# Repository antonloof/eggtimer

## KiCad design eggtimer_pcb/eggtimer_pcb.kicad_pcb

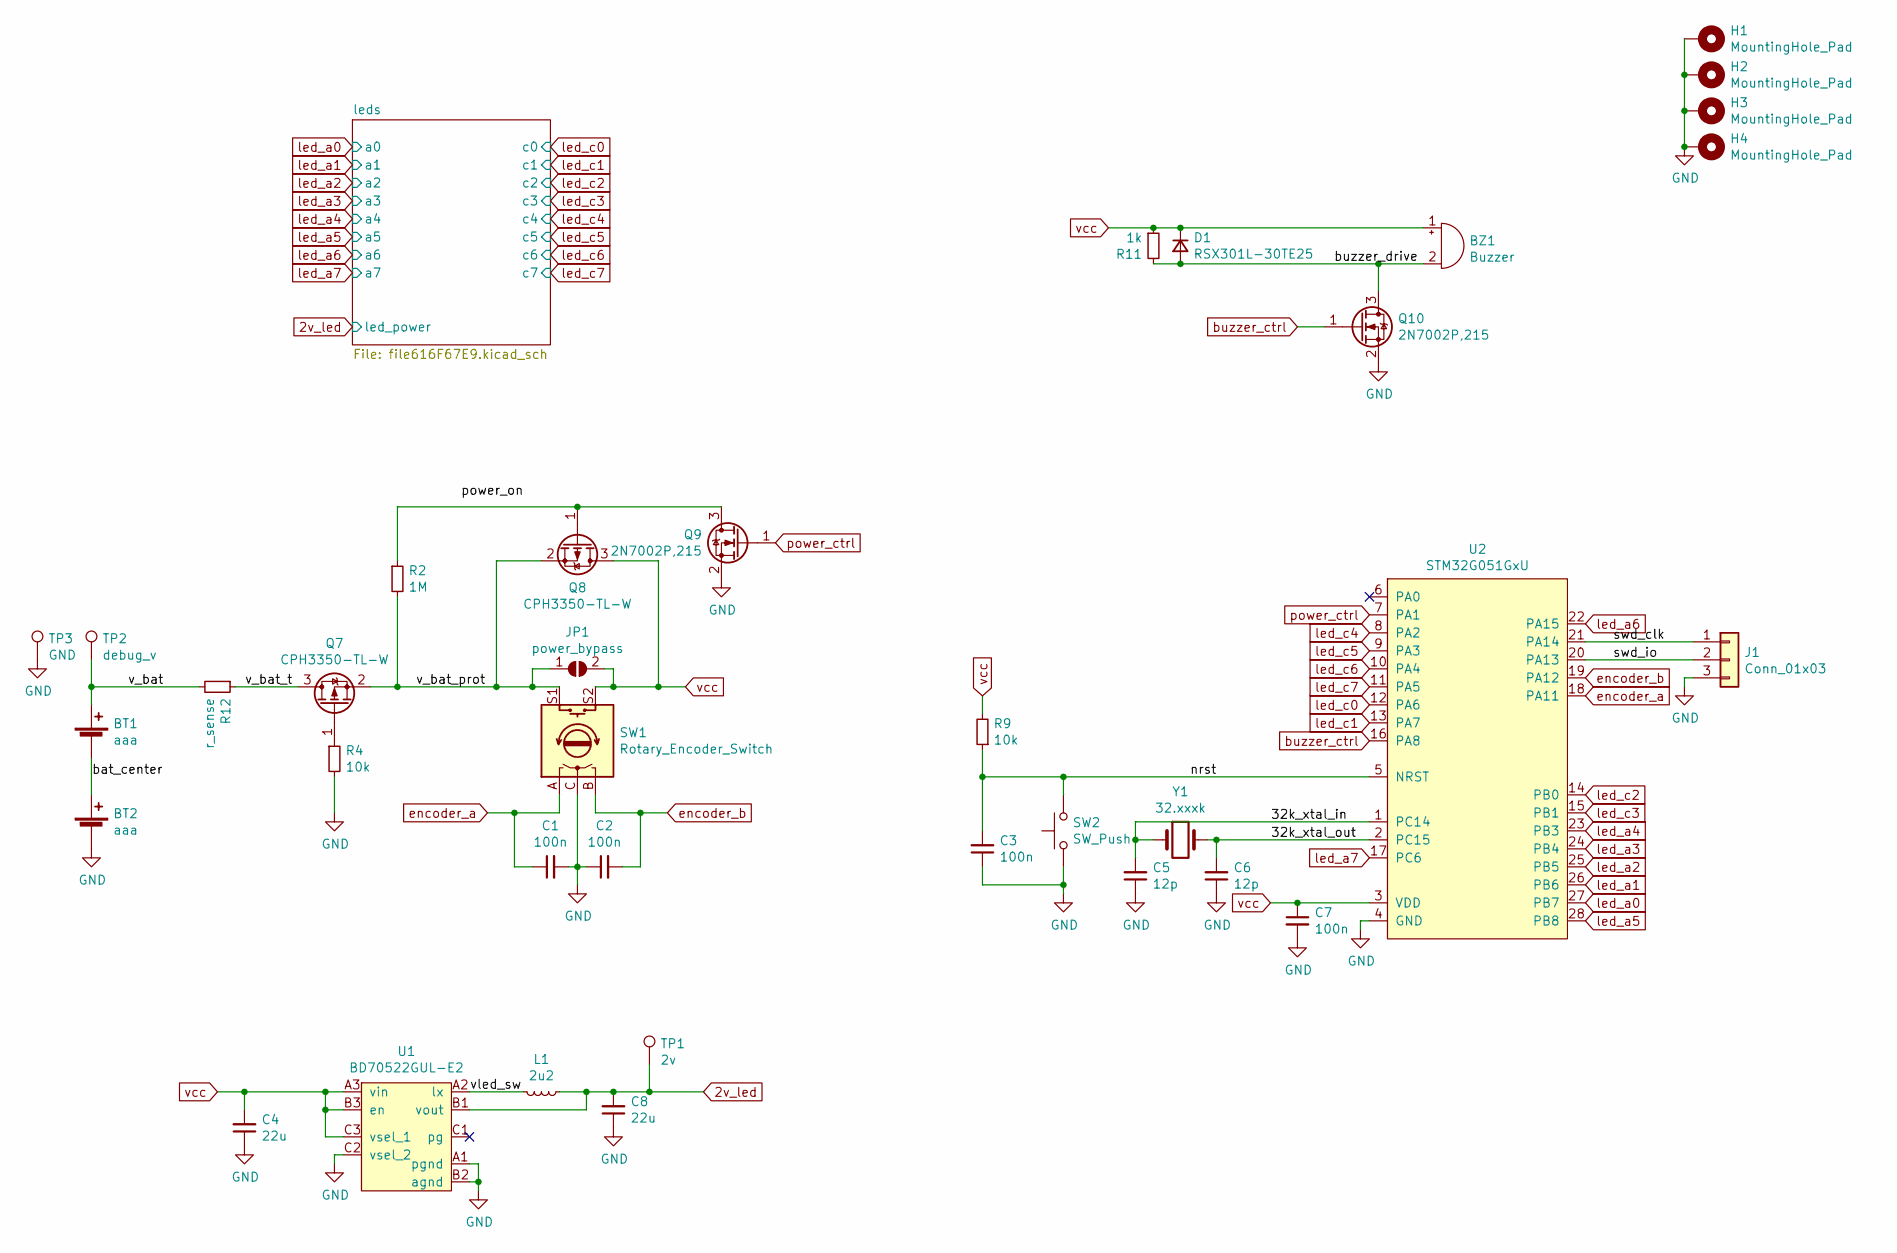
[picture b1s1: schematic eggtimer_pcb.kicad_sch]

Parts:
BT1, BT2: aaa; BatteryHolder_Keystone_2466_1xAAA
BZ1: Buzzer; buzzer_d14_p5
C1, C2, C3, C7: 100n; C_0603_1608Metric
C4, C8: 22u; C_0603_1608Metric
C5, C6: 12p; C_0603_1608Metric
D1: RSX301L-30TE25; smd_diode_sod_106
H1, H2, H3, H4: MountingHole_Pad; MountingHole_2.7mm_M2.5_DIN965_Pad
J1: Conn_01x03; PinHeader_1x03_P2.54mm_Vertical
JP1: power_bypass; SolderJumper-2_P1.3mm_Open_TrianglePad1.0x1.5mm
L1: 2u2; L_Wuerth_MAPI-2010
Q7, Q8: CPH3350-TL-W; SOT-23_Handsoldering
Q9, Q10: 2N7002P,215; SOT-23_Handsoldering
R2: 1M; R_0603_1608Metric_Pad0.98x0.95mm_HandSolder
R4, R9: 10k; R_0603_1608Metric_Pad0.98x0.95mm_HandSolder
R11: 1k; R_0603_1608Metric_Pad0.98x0.95mm_HandSolder
R12: r_sense; R_0603_1608Metric_Pad0.98x0.95mm_HandSolder
SW1: Rotary_Encoder_Switch; RotaryEncoder_Alps_EC11E-Switch_Vertical_H20mm
SW2: SW_Push; push_sw_purple
TP1: 2v; TestPoint_Pad_D2.0mm
TP2: debug_v; TestPoint_Pad_D1.5mm
TP3: GND; TestPoint_Pad_D1.5mm
U1: BD70522GUL-E2; BGA-9_3x3_1.76x1.56mm
U2: STM32G051GxU; QFN-28_4x4mm_P0.5mm
Y1: 32.xxxk; Crystal_Round_D3.0mm_Vertical

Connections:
2v_led: C8.2, L1.1, TP1.1, U1.B1 (vout); also elsewhere on the board
/32k_xtal_in: C6.2, U2.2 (PC15), Y1.2
/32k_xtal_out: C5.2, U2.1 (PC14), Y1.1
/bat_center: BT1.2 (-), BT2.1 (+)
/buzzer_drive: BZ1.2 (+), D1.2 (A), Q10.3 (D), R11.2
/nrst: C3.2, R9.1, SW2.2, U2.5 (NRST)
/swd_clk: J1.1, U2.21 (PA14)
/swd_io: J1.2, U2.20 (PA13)
/v_bat: BT1.1 (+), R12.2, TP2.1
/v_bat_prot: JP1.1 (A), Q7.2 (S), Q8.2 (S), R2.2, SW1.S1
/v_bat_t: Q7.3 (D), R12.1
/vled_sw: L1.2, U1.A2 (lx)
GND: BT2.2 (-), C1.2, C2.1, C3.1, C4.1, C5.1, C6.1, C7.2, C8.1, H1.1, H2.1, H3.1, H4.1, J1.3, Q9.2 (S), Q10.2 (S), R4.2, SW1.C, SW2.1, TP3.1, U1.A1 (pgnd), U1.B2 (agnd), U1.C2 (vsel_2), U2.4 (GND)
unnamed: Q7.1 (G), R4.1
unnamed: Q8.1 (G), Q9.3 (D), R2.1
buzzer_ctrl: Q10.1 (G), U2.16 (PA8)
encoder_a: C1.1, SW1.A, U2.18 (PA11)
encoder_b: C2.2, SW1.B, U2.19 (PA12)
led_a0: U2.27 (PB7); also elsewhere on the board
led_a1: U2.26 (PB6); also elsewhere on the board
led_a2: U2.25 (PB5); also elsewhere on the board
led_a3: U2.24 (PB4); also elsewhere on the board
led_a4: U2.23 (PB3); also elsewhere on the board
led_a5: U2.28 (PB8); also elsewhere on the board
led_a6: U2.22 (PA15); also elsewhere on the board
led_a7: U2.17 (PC6); also elsewhere on the board
led_c0: U2.12 (PA6); also elsewhere on the board
led_c1: U2.13 (PA7); also elsewhere on the board
led_c2: U2.14 (PB0); also elsewhere on the board
led_c3: U2.15 (PB1); also elsewhere on the board
led_c4: U2.8 (PA2); also elsewhere on the board
led_c5: U2.9 (PA3); also elsewhere on the board
led_c6: U2.10 (PA4); also elsewhere on the board
led_c7: U2.11 (PA5); also elsewhere on the board
power_ctrl: Q9.1 (G), U2.7 (PA1)
vcc: BZ1.1 (-), C4.2, C7.1, D1.1 (K), JP1.2 (B), Q8.3 (D), R9.2, R11.1, SW1.S2, U1.A3 (vin), U1.B3 (en), U1.C3 (vsel_1), U2.3 (VDD)

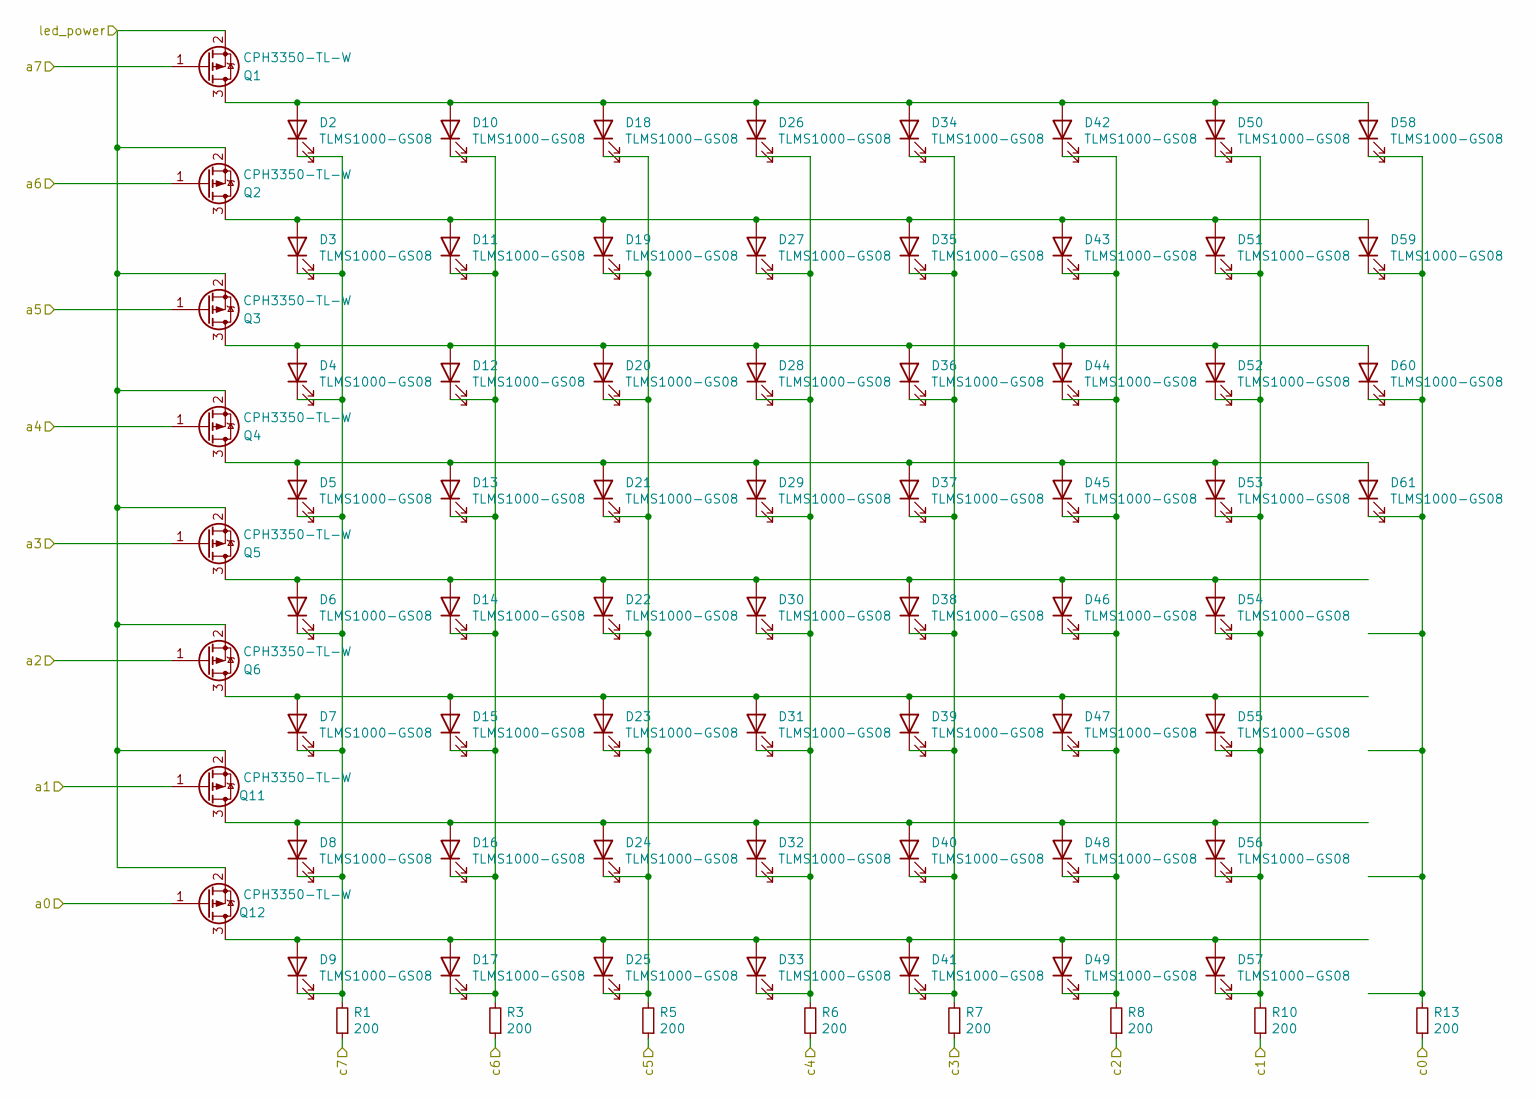
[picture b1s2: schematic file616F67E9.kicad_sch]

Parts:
D2, D3, D4, D5, D6, D7, D8, D9, D10, D11, D12, D13, D14, D15, D16, D17, D18, D19, D20, D21, D22, D23, D24, D25, D26, D27, D28, D29, D30, D31, D32, D33, D34, D35, D36, D37, D38, D39, D40, D41, D42, D43, D44, D45, D46, D47, D48, D49, D50, D51, D52, D53, D54, D55, D56, D57, D58, D59, D60, D61: TLMS1000-GS08; LED_0603_1608Metric_Pad1.05x0.95mm_HandSolder
Q1, Q2, Q3, Q4, Q5, Q6, Q11, Q12: CPH3350-TL-W; SOT-23_Handsoldering
R1, R3, R5, R6, R7, R8, R10, R13: 200; R_0603_1608Metric_Pad0.98x0.95mm_HandSolder

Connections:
2v_led: Q1.2 (S), Q2.2 (S), Q3.2 (S), Q4.2 (S), Q5.2 (S), Q6.2 (S), Q11.2 (S), Q12.2 (S); also elsewhere on the board
unnamed: D2.1 (K), D3.1 (K), D4.1 (K), D5.1 (K), D6.1 (K), D7.1 (K), D8.1 (K), D9.1 (K), R1.2
unnamed: D10.1 (K), D11.1 (K), D12.1 (K), D13.1 (K), D14.1 (K), D15.1 (K), D16.1 (K), D17.1 (K), R3.2
unnamed: D2.2 (A), D10.2 (A), D18.2 (A), D26.2 (A), D34.2 (A), D42.2 (A), D50.2 (A), D58.2 (A), Q1.3 (D)
unnamed: D3.2 (A), D11.2 (A), D19.2 (A), D27.2 (A), D35.2 (A), D43.2 (A), D51.2 (A), D59.2 (A), Q2.3 (D)
unnamed: D4.2 (A), D12.2 (A), D20.2 (A), D28.2 (A), D36.2 (A), D44.2 (A), D52.2 (A), D60.2 (A), Q3.3 (D)
unnamed: D5.2 (A), D13.2 (A), D21.2 (A), D29.2 (A), D37.2 (A), D45.2 (A), D53.2 (A), D61.2 (A), Q4.3 (D)
unnamed: D6.2 (A), D14.2 (A), D22.2 (A), D30.2 (A), D38.2 (A), D46.2 (A), D54.2 (A), Q5.3 (D)
unnamed: D7.2 (A), D15.2 (A), D23.2 (A), D31.2 (A), D39.2 (A), D47.2 (A), D55.2 (A), Q6.3 (D)
unnamed: D8.2 (A), D16.2 (A), D24.2 (A), D32.2 (A), D40.2 (A), D48.2 (A), D56.2 (A), Q11.3 (D)
unnamed: D9.2 (A), D17.2 (A), D25.2 (A), D33.2 (A), D41.2 (A), D49.2 (A), D57.2 (A), Q12.3 (D)
unnamed: D18.1 (K), D19.1 (K), D20.1 (K), D21.1 (K), D22.1 (K), D23.1 (K), D24.1 (K), D25.1 (K), R5.2
unnamed: D26.1 (K), D27.1 (K), D28.1 (K), D29.1 (K), D30.1 (K), D31.1 (K), D32.1 (K), D33.1 (K), R6.2
unnamed: D34.1 (K), D35.1 (K), D36.1 (K), D37.1 (K), D38.1 (K), D39.1 (K), D40.1 (K), D41.1 (K), R7.2
unnamed: D42.1 (K), D43.1 (K), D44.1 (K), D45.1 (K), D46.1 (K), D47.1 (K), D48.1 (K), D49.1 (K), R8.2
unnamed: D50.1 (K), D51.1 (K), D52.1 (K), D53.1 (K), D54.1 (K), D55.1 (K), D56.1 (K), D57.1 (K), R10.2
unnamed: D58.1 (K), D59.1 (K), D60.1 (K), D61.1 (K), R13.2
led_a0: Q12.1 (G); also elsewhere on the board
led_a1: Q11.1 (G); also elsewhere on the board
led_a2: Q6.1 (G); also elsewhere on the board
led_a3: Q5.1 (G); also elsewhere on the board
led_a4: Q4.1 (G); also elsewhere on the board
led_a5: Q3.1 (G); also elsewhere on the board
led_a6: Q2.1 (G); also elsewhere on the board
led_a7: Q1.1 (G); also elsewhere on the board
led_c0: R13.1; also elsewhere on the board
led_c1: R10.1; also elsewhere on the board
led_c2: R8.1; also elsewhere on the board
led_c3: R7.1; also elsewhere on the board
led_c4: R6.1; also elsewhere on the board
led_c5: R5.1; also elsewhere on the board
led_c6: R3.1; also elsewhere on the board
led_c7: R1.1; also elsewhere on the board

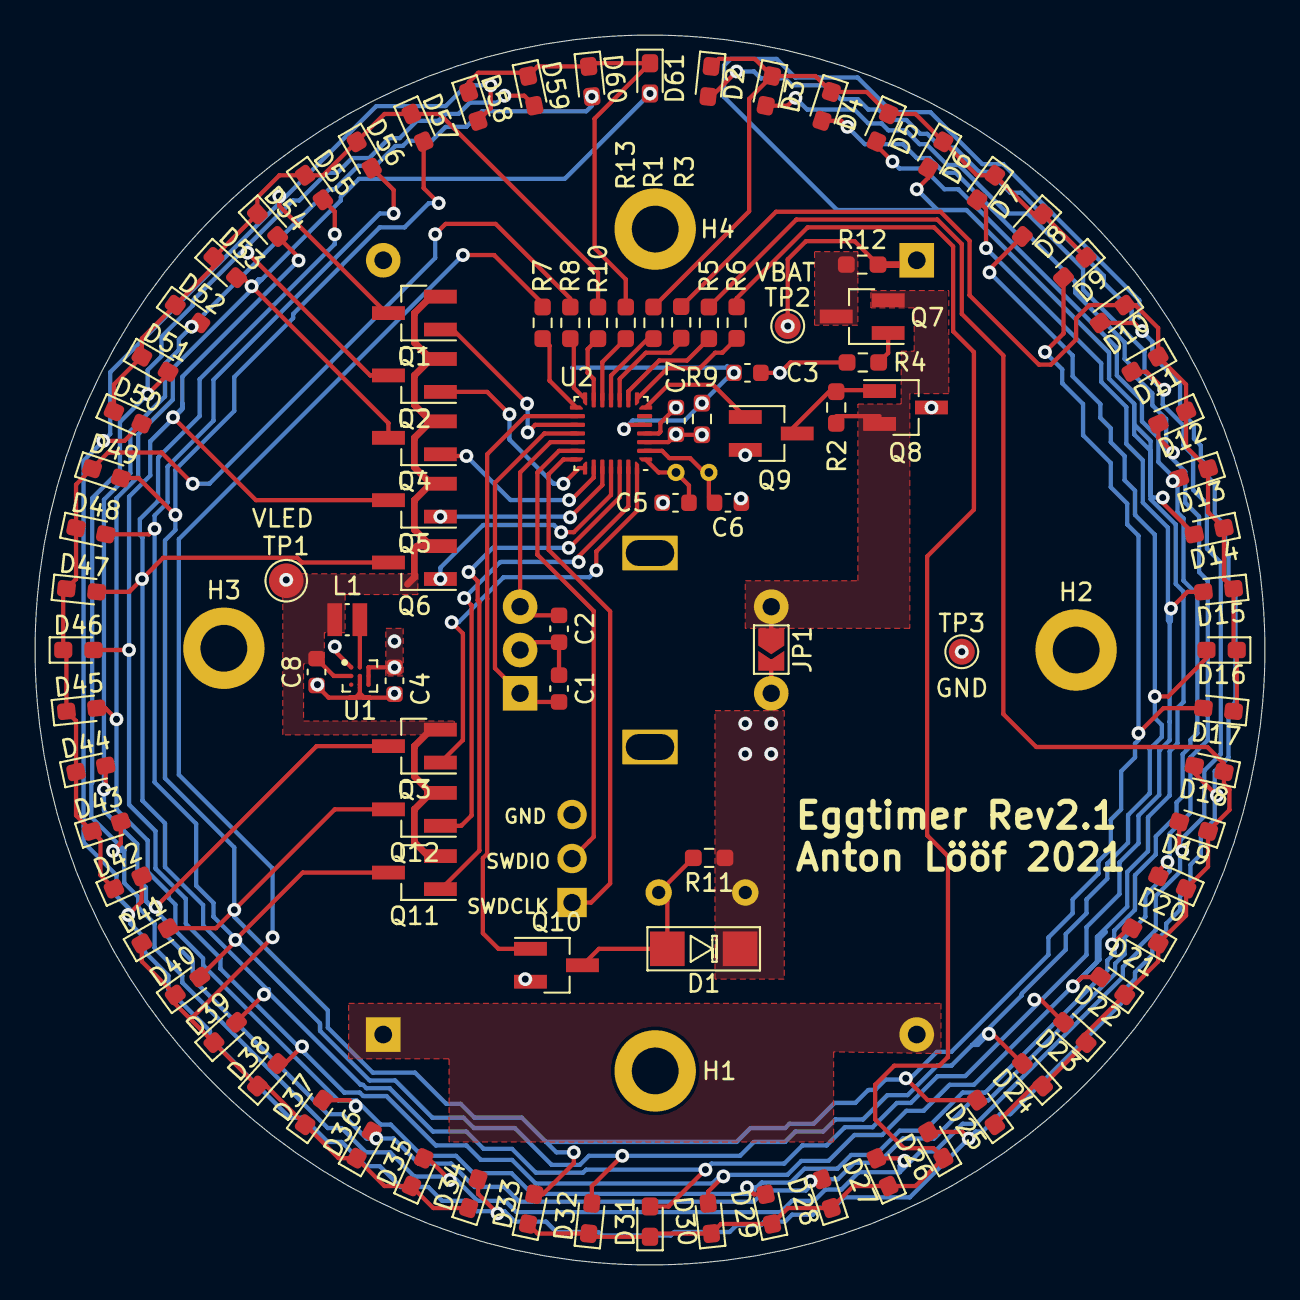
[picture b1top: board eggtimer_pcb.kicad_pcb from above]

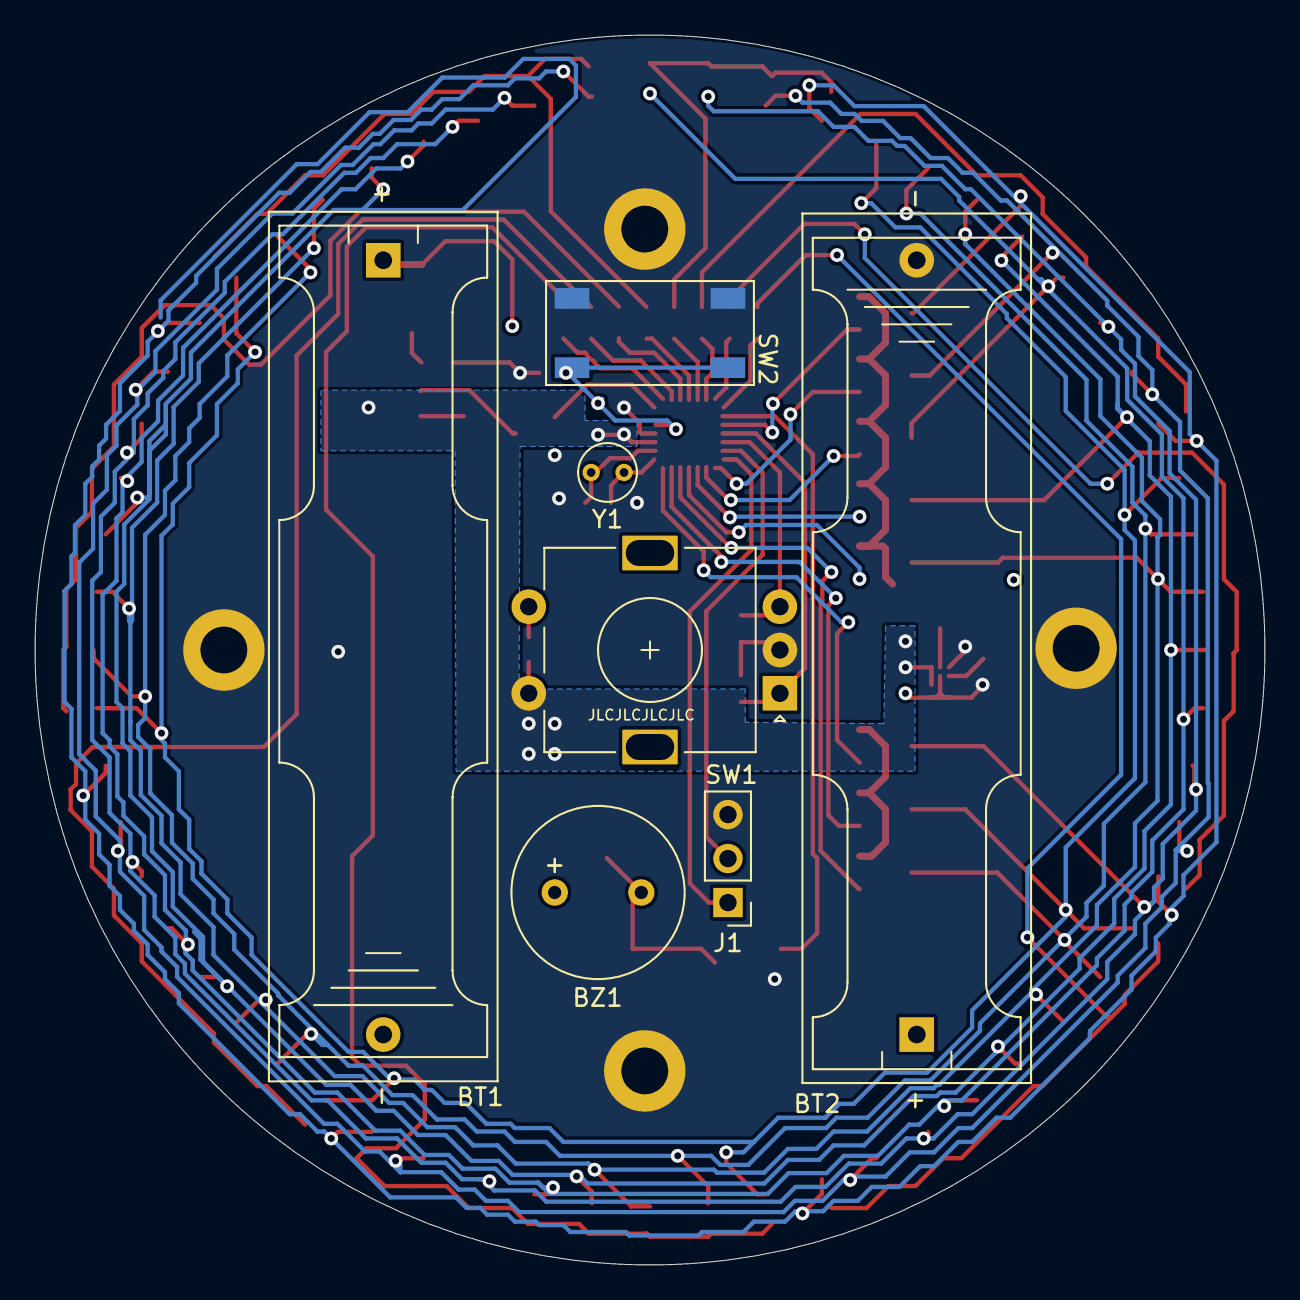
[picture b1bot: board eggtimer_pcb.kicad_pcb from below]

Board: 2 copper layers, 71.0 x 71.0 mm, 112 parts (7 on the bottom side), 52 nets.

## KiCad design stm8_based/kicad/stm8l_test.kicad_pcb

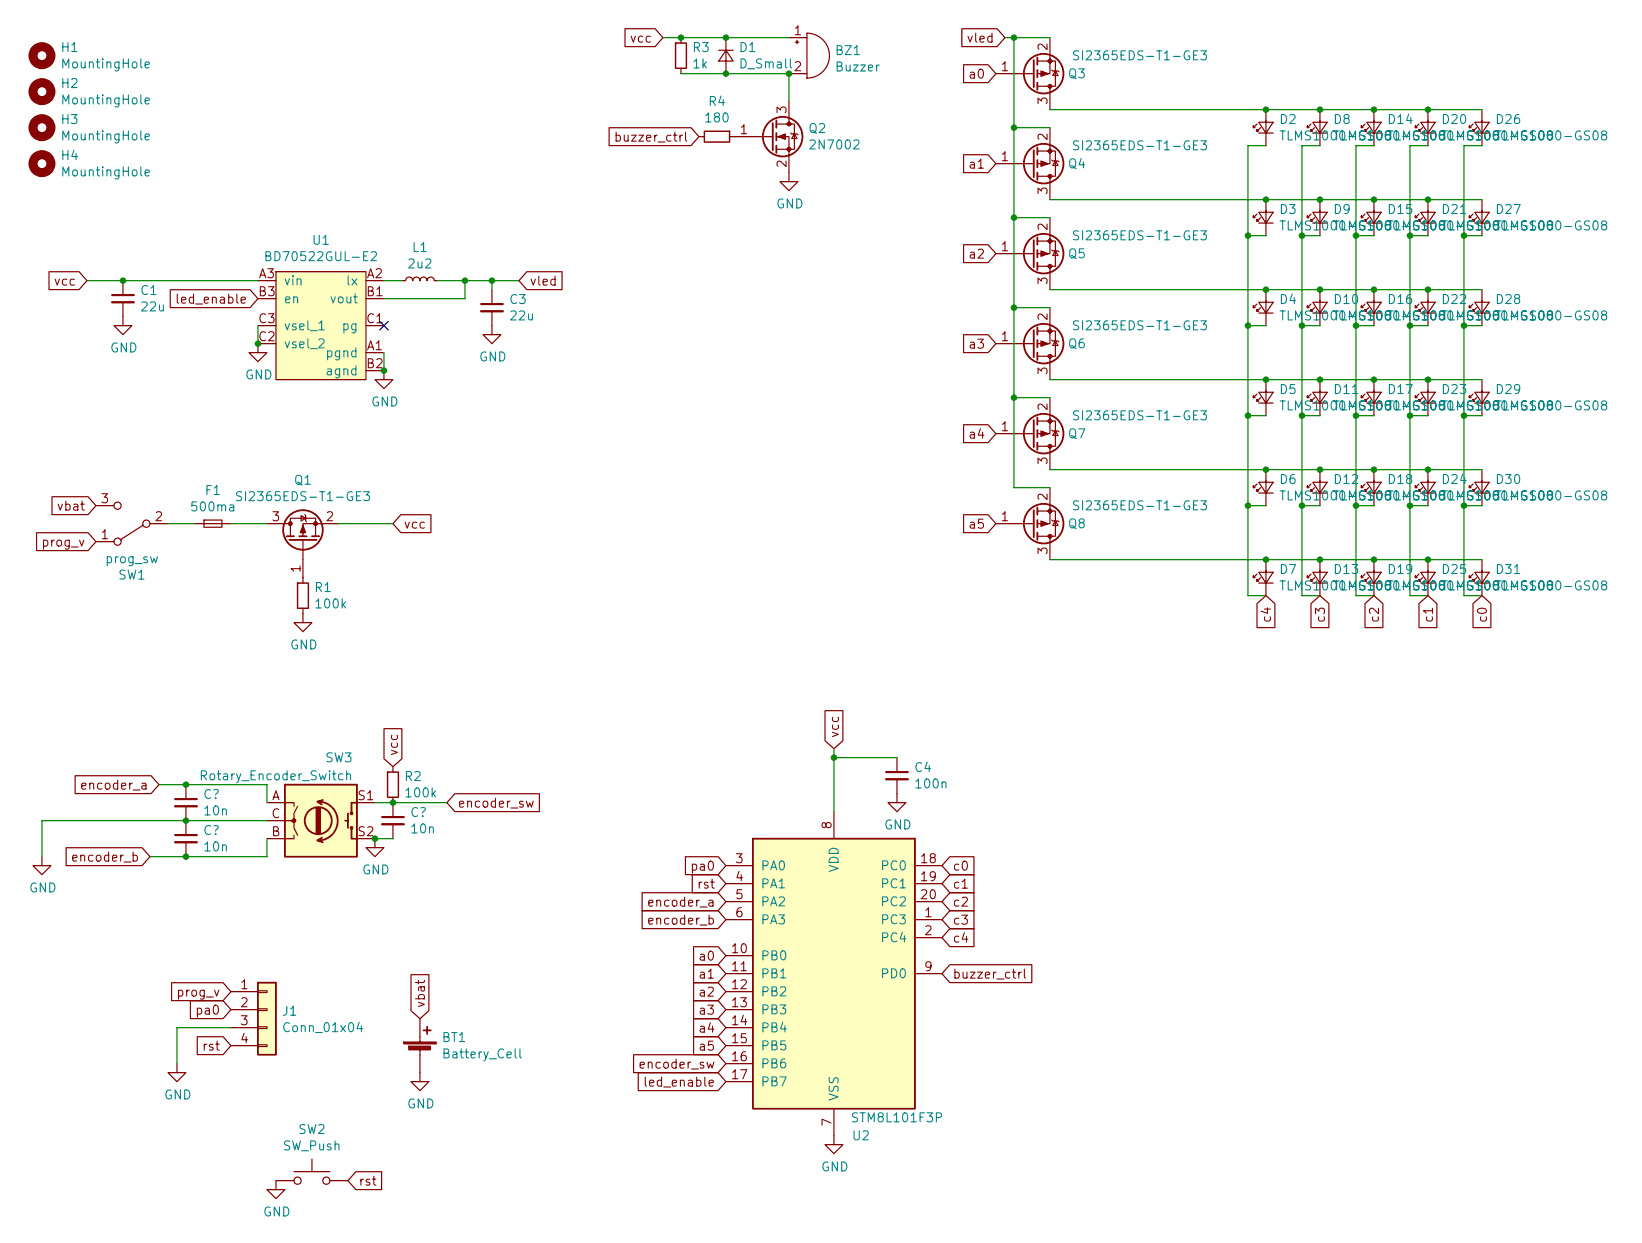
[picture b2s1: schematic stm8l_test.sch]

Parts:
BT1: Battery_Cell; BatteryHolder_Keystone_3002_1x2032
BZ1: Buzzer; buzzer_d14_p5
C1, C3: 22u; C_0603_1608Metric_Pad1.05x0.95mm_HandSolder
C4: 100n; C_0603_1608Metric_Pad1.05x0.95mm_HandSolder
D1: D_Small; D_1210_3225Metric_Pad1.42x2.65mm_HandSolder
D2, D3, D4, D5, D6, D7, D8, D9, D10, D11, D12, D13, D14, D15, D16, D17, D18, D19, D20, D21, D22, D23, D24, D25, D26, D27, D28, D29, D30, D31: TLMS1000-GS08; LED_0603_1608Metric_Pad1.05x0.95mm_HandSolder
F1: 500ma; Fuse_1206_3216Metric_Pad1.42x1.75mm_HandSolder
H1, H2, H3, H4: MountingHole; MountingHole_2.7mm_M2.5
J1: Conn_01x04; TSM-104-01-L-SH
L1: 2u2; L_Wuerth_WE-PD-Typ-7345
Q1, Q3, Q4, Q5, Q6, Q7, Q8: SI2365EDS-T1-GE3; SOT-23_Handsoldering
Q2: 2N7002; SOT-23
R1, R2: 100k; R_0603_1608Metric_Pad1.05x0.95mm_HandSolder
R3: 1k; R_0603_1608Metric_Pad1.05x0.95mm_HandSolder
R4: 180; R_0603_1608Metric_Pad1.05x0.95mm_HandSolder
SW1: prog_sw; TSM-103-01-l_SH
SW2: SW_Push; push_sw_purple
SW3: Rotary_Encoder_Switch; RotaryEncoder_Alps_EC11E-Switch_Vertical_H20mm
U1: BD70522GUL-E2; BGA-9_3x3_1.76x1.56mm
U2: STM8L101F3P; TSSOP-20_4.4x6.5mm_P0.65mm

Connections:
GND: BT1.2 (-), C1.2, C3.2, C4.2, J1.3, Q2.2 (S), R1.2, SW2.1, SW3.C, SW3.S2, U1.A1 (pgnd), U1.B2 (agnd), U1.C2 (vsel_2), U1.C3 (vsel_1), U2.7 (VSS)
unnamed: BZ1.2 (+), D1.2 (A), Q2.3 (D), R3.2
unnamed: D4.2 (A), D10.2 (A), D16.2 (A), D22.2 (A), D28.2 (A), Q5.3 (D)
unnamed: D5.2 (A), D11.2 (A), D17.2 (A), D23.2 (A), D29.2 (A), Q6.3 (D)
unnamed: D6.2 (A), D12.2 (A), D18.2 (A), D24.2 (A), D30.2 (A), Q7.3 (D)
unnamed: D7.2 (A), D13.2 (A), D19.2 (A), D25.2 (A), D31.2 (A), Q8.3 (D)
unnamed: D2.2 (A), D8.2 (A), D14.2 (A), D20.2 (A), D26.2 (A), Q3.3 (D)
unnamed: D3.2 (A), D9.2 (A), D15.2 (A), D21.2 (A), D27.2 (A), Q4.3 (D)
unnamed: F1.1, SW1.2 (B)
unnamed: F1.2, Q1.3 (D)
unnamed: L1.1, U1.A2 (lx)
unnamed: Q1.1 (G), R1.1
unnamed: Q2.1 (G), R4.1
a0: Q3.1 (G), U2.10 (PB0)
a1: Q4.1 (G), U2.11 (PB1)
a2: Q5.1 (G), U2.12 (PB2)
a3: Q6.1 (G), U2.13 (PB3)
a4: Q7.1 (G), U2.14 (PB4)
a5: Q8.1 (G), U2.15 (PB5)
buzzer_ctrl: R4.2, U2.9 (PD0)
c0: D26.1 (K), D27.1 (K), D28.1 (K), D29.1 (K), D30.1 (K), D31.1 (K), U2.18 (PC0)
c1: D20.1 (K), D21.1 (K), D22.1 (K), D23.1 (K), D24.1 (K), D25.1 (K), U2.19 (PC1)
c2: D14.1 (K), D15.1 (K), D16.1 (K), D17.1 (K), D18.1 (K), D19.1 (K), U2.20 (PC2)
c3: D8.1 (K), D9.1 (K), D10.1 (K), D11.1 (K), D12.1 (K), D13.1 (K), U2.1 (PC3)
c4: D2.1 (K), D3.1 (K), D4.1 (K), D5.1 (K), D6.1 (K), D7.1 (K), U2.2 (PC4)
encoder_a: SW3.A, U2.5 (PA2)
encoder_b: SW3.B, U2.6 (PA3)
encoder_sw: R2.2, SW3.S1, U2.16 (PB6)
led_enable: U1.B3 (en), U2.17 (PB7)
pa0: J1.2, U2.3 (PA0)
prog_v: J1.1, SW1.1 (A)
rst: J1.4, SW2.2, U2.4 (PA1)
vled: C3.1, L1.2, Q3.2 (S), Q4.2 (S), Q5.2 (S), Q6.2 (S), Q7.2 (S), Q8.2 (S), U1.B1 (vout)

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
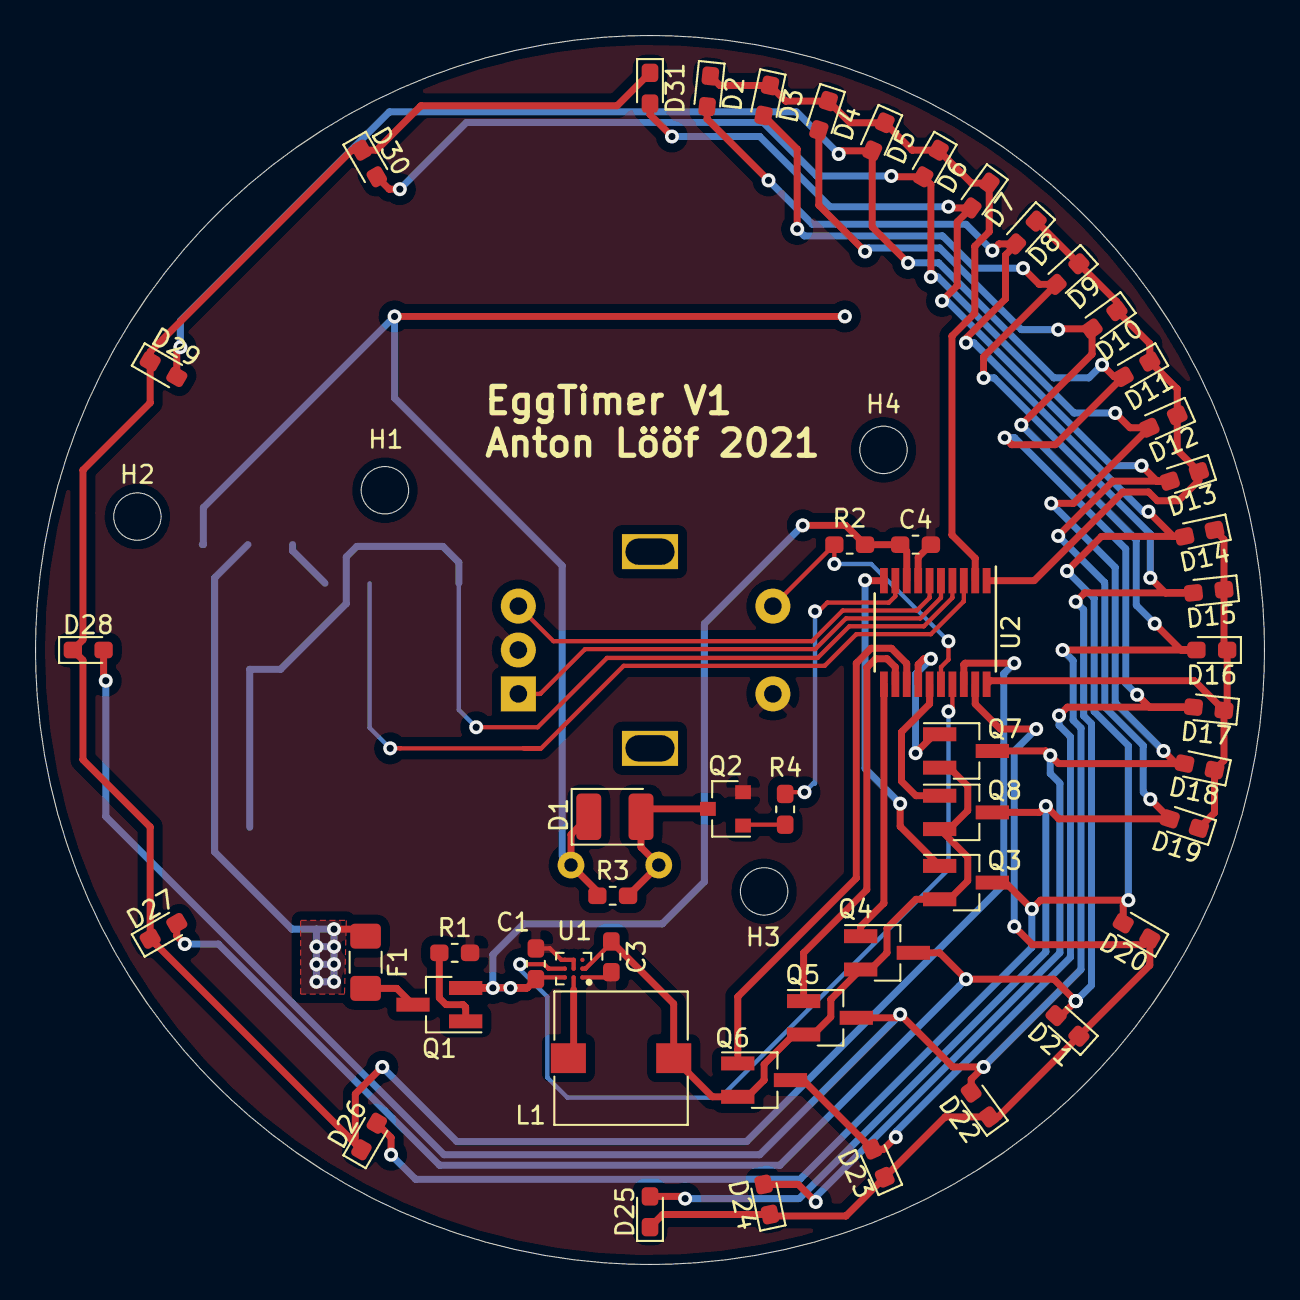
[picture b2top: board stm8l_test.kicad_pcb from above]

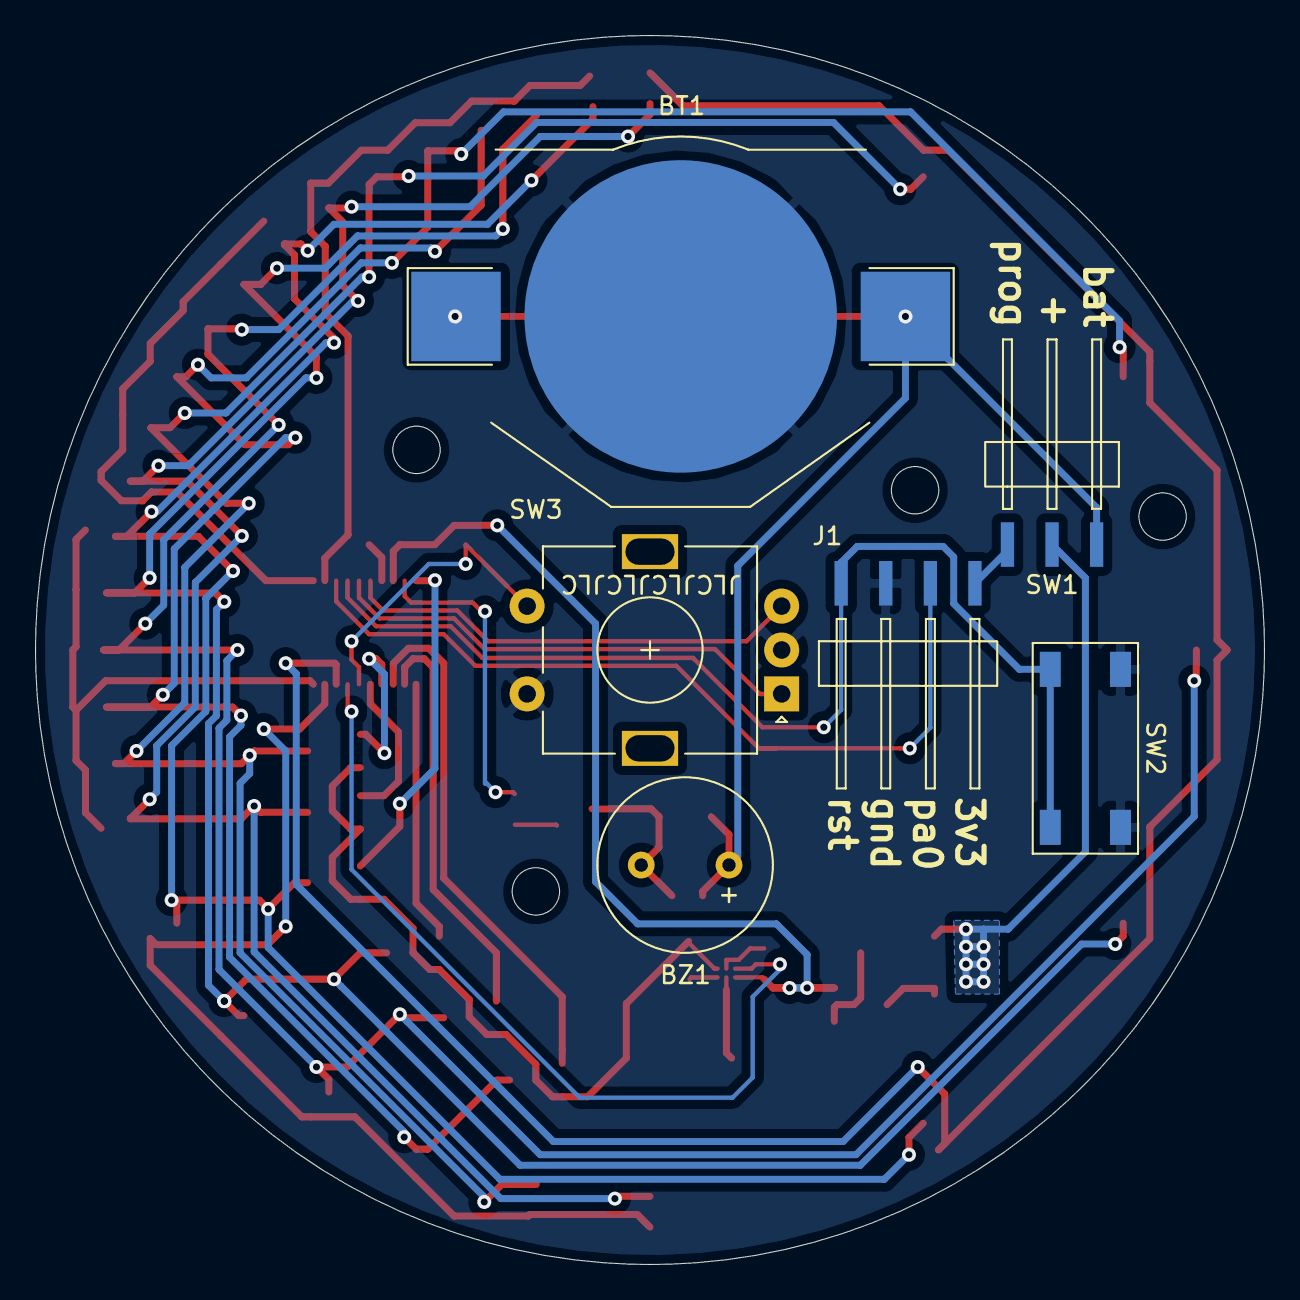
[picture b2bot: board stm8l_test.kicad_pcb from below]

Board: 2 copper layers, 70.0 x 70.0 mm, 60 parts (6 on the bottom side), 35 nets.

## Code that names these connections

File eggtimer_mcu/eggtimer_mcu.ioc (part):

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Mcu.Name=STM32G051G(6-8)Ux
Mcu.Package=UFQFPN28
Mcu.UserName=STM32G051G6Ux
PA1.GPIOParameters=GPIO_Label
PA1.GPIO_Label=power_ctrl
PA1.Signal=GPIO_Output
PA11\ [PA9].GPIOParameters=GPIO_Label
PA11\ [PA9].GPIO_Label=encoder_a
PA11\ [PA9].Signal=GPXTI11
PA12\ [PA10].GPIOParameters=GPIO_Label
PA12\ [PA10].GPIO_Label=encoder_b
PA12\ [PA10].Signal=GPXTI12
PA13.Mode=Serial_Wire
PA13.Signal=SYS_SWDIO
PA14-BOOT0.Mode=Serial_Wire
PA14-BOOT0.Signal=SYS_SWCLK
PA15.GPIOParameters=GPIO_Label
PA15.GPIO_Label=led_a6
PA15.Signal=GPIO_Output
PA2.GPIOParameters=GPIO_Label
PA2.GPIO_Label=led_c4
PA2.Signal=GPIO_Output
PA3.GPIOParameters=GPIO_Label,GPIO_ModeDefaultOutputPP
PA3.GPIO_Label=led_c5
PA3.GPIO_ModeDefaultOutputPP=GPIO_MODE_OUTPUT_OD
PA3.Signal=GPIO_Output
PA4.GPIOParameters=GPIO_Label,GPIO_ModeDefaultOutputPP
PA4.GPIO_Label=led_c6
PA4.GPIO_ModeDefaultOutputPP=GPIO_MODE_OUTPUT_OD
PA4.Signal=GPIO_Output
PA5.GPIOParameters=GPIO_Label,GPIO_ModeDefaultOutputPP
PA5.GPIO_Label=led_c7
PA5.GPIO_ModeDefaultOutputPP=GPIO_MODE_OUTPUT_OD
PA5.Signal=GPIO_Output
PA6.GPIOParameters=GPIO_Label,GPIO_ModeDefaultOutputPP
PA6.GPIO_Label=led_c0
PA6.GPIO_ModeDefaultOutputPP=GPIO_MODE_OUTPUT_OD
PA6.Signal=GPIO_Output
PA7.GPIOParameters=GPIO_Label,GPIO_ModeDefaultOutputPP
PA7.GPIO_Label=led_c1
PA7.GPIO_ModeDefaultOutputPP=GPIO_MODE_OUTPUT_OD
PA7.Signal=GPIO_Output
PA8.GPIOParameters=GPIO_Label
PA8.GPIO_Label=buzzer_ctrl
PA8.Signal=S_TIM1_CH1
PB0.GPIOParameters=GPIO_Label,GPIO_ModeDefaultOutputPP
PB0.GPIO_Label=led_c2
PB0.GPIO_ModeDefaultOutputPP=GPIO_MODE_OUTPUT_OD
PB0.Signal=GPIO_Output
PB1.GPIOParameters=GPIO_Label
PB1.GPIO_Label=led_c3
PB1.Signal=GPIO_Output
PB3.GPIOParameters=GPIO_Label,GPIO_ModeDefaultOutputPP
PB3.GPIO_Label=led_a4
PB3.GPIO_ModeDefaultOutputPP=GPIO_MODE_OUTPUT_PP
PB3.Signal=GPIO_Output
PB4.GPIOParameters=GPIO_Label,GPIO_ModeDefaultOutputPP
PB4.GPIO_Label=led_a3
PB4.GPIO_ModeDefaultOutputPP=GPIO_MODE_OUTPUT_PP
PB4.Signal=GPIO_Output
PB5.GPIOParameters=GPIO_Label,GPIO_ModeDefaultOutputPP
PB5.GPIO_Label=led_a2
PB5.GPIO_ModeDefaultOutputPP=GPIO_MODE_OUTPUT_PP
PB5.Signal=GPIO_Output
PB6.GPIOParameters=GPIO_Label,GPIO_ModeDefaultOutputPP
PB6.GPIO_Label=led_a1
PB6.GPIO_ModeDefaultOutputPP=GPIO_MODE_OUTPUT_PP
PB6.Signal=GPIO_Output
PB7.GPIOParameters=GPIO_Label,GPIO_ModeDefaultOutputPP
PB7.GPIO_Label=led_a0
PB7.GPIO_ModeDefaultOutputPP=GPIO_MODE_OUTPUT_PP
PB7.Signal=GPIO_Output
PB8.GPIOParameters=GPIO_Label,GPIO_ModeDefaultOutputPP
PB8.GPIO_Label=led_a5
PB8.GPIO_ModeDefaultOutputPP=GPIO_MODE_OUTPUT_PP
PB8.Signal=GPIO_Output
PC14-OSC32_IN\ (PC14).Mode=LSE-External-Oscillator
PC14-OSC32_IN\ (PC14).Signal=RCC_OSC32_IN
PC15-OSC32_OUT\ (PC15).Mode=LSE-External-Oscillator
PC15-OSC32_OUT\ (PC15).Signal=RCC_OSC32_OUT
PC6.GPIOParameters=GPIO_Label
PC6.GPIO_Label=led_a7
PC6.Signal=GPIO_Output
RCC.HSE_VALUE=8000000
RCC.SYSCLKFreq_VALUE=16000000
board=custom

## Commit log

2021-04-11 Add test PCB
2021-04-11 stuff
2021-04-23 Rev1 deb pcb
    eta ets not stronk
2021-05-10 thinking about the solution, picking leds et al
2021-05-11 Pdb work, schema done
2021-05-11 Place components and initial routing
2021-05-13 PCB rev1 ordered
2021-07-18 Interrupts work better now änna
2021-07-19 Now with blinky leds
2021-07-30 Leds and buzzer works
    added debounce caps
2021-07-30 update ignore
2021-10-14 Move old stuff using mcu that i cant buy anymore
2021-10-15 Add new pcb with stm32g0
2021-10-15 Schema is done
    some layout work
2021-10-16 Add pcb rev2
    also design planetary gears for mechanics and make sure they fit
2021-10-19 remove random nc
2021-10-19 MORE LEDS
2021-10-27 Finalize rev2.1 pcb
    make sure that schema is up to date with stmcubemx
2021-10-31 fix some distances
2022-01-06 Use kicad6
